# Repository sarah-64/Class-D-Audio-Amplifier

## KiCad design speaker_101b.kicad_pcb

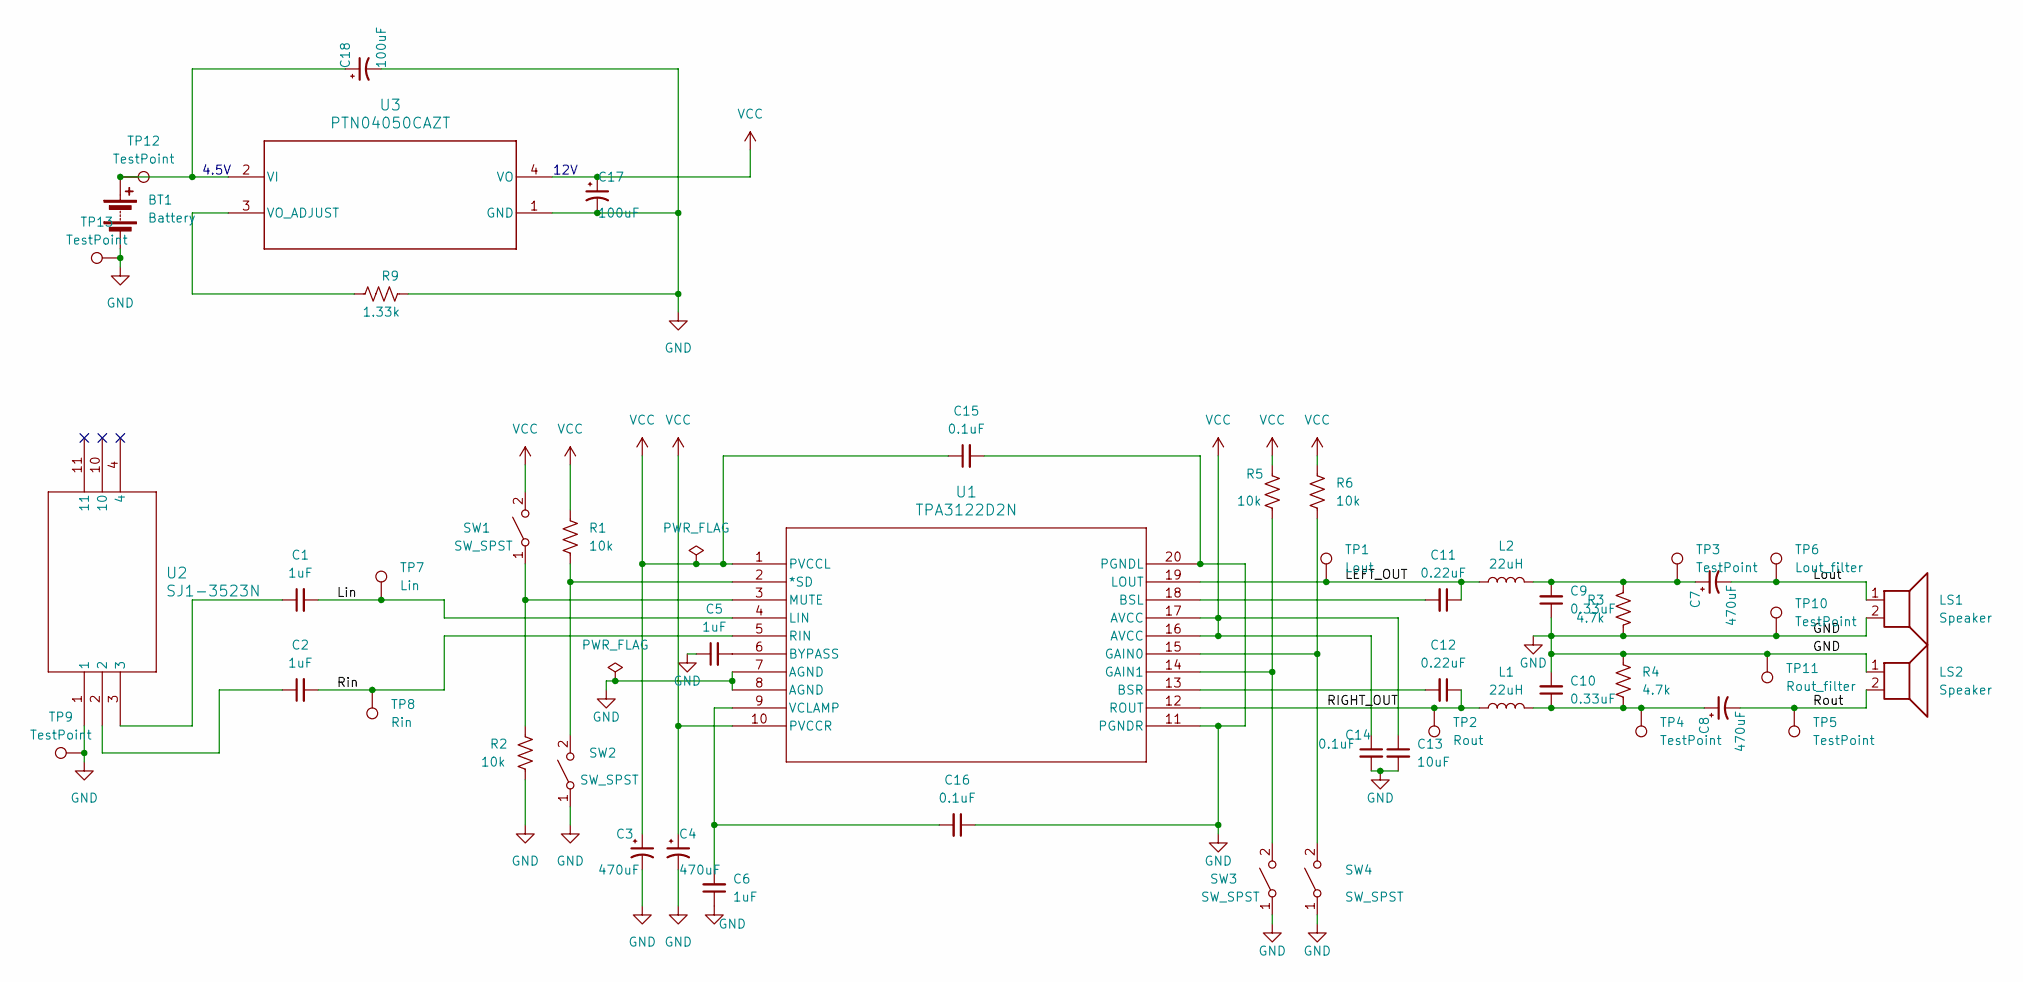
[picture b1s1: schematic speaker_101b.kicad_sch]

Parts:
BT1: Battery; R_1206_3216Metric_Pad1.30x1.75mm_HandSolder
C1, C2, C5, C6: 1uF; CAP_CL10_SAM
C3, C4, C7, C8: 470uF; CAP_EEE_J16_PAN
C9, C10: 0.33uF; CAP_CL10_SAM
C11, C12: 0.22uF; CAP_GCM155_MUR
C13: 10uF; CAP_CL10_SAM
C14: 0.1uF; CAP_CL10_SAM
C15, C16: 0.1uF; CC0805N_YAG
C17, C18: 100uF; CAP_CL10_SAM
L1, L2: 22uH; L_1206_3216Metric
LS1, LS2: Speaker; R_1206_3216Metric
R1, R2, R5, R6: 10k; R_1206_3216Metric
R3, R4: 4.7k; R_1206_3216Metric
R9: 1.33k; R_1206_3216Metric
SW1, SW2, SW3, SW4: SW_SPST; R_1206_3216Metric
TP1: Lout; TestPoint_Pad_3.0x3.0mm
TP2: Rout; TestPoint_Pad_3.0x3.0mm
TP3, TP4, TP5, TP9, TP10, TP12, TP13: TestPoint; TestPoint_Pad_3.0x3.0mm
TP6: Lout_filter; TestPoint_Pad_3.0x3.0mm
TP7: Lin; TestPoint_Pad_3.0x3.0mm
TP8: Rin; TestPoint_Pad_3.0x3.0mm
TP11: Rout_filter; TestPoint_Pad_3.0x3.0mm
U1: TPA3122D2N; N20
U2: SJ1-3523N; SJ1-3523N_CUD
U3: PTN04050CAZT; EUV0004A

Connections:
/LEFT_OUT: C11.1, L2.1, TP1.1, U1.19 (LOUT)
/Lin: C1.2, TP7.1, U1.4 (LIN)
/Lout: C7.2, LS1.1, TP6.1
/RIGHT_OUT: C12.1, L1.1, TP2.1, U1.12 (ROUT)
/Rin: C2.2, TP8.1, U1.5 (RIN)
/Rout: C8.2, LS2.2, TP5.1
GND: BT1.2 (-), C3.2, C4.2, C5.1, C6.1, C9.1, C10.2, C13.2, C14.2, C15.2, C16.1, C17.2, C18.2, LS1.2, LS2.1, R2.2, R3.2, R4.1, R9.2, SW2.1 (A), SW3.1 (A), SW4.1 (A), TP9.1, TP10.1, TP11.1, TP13.1, U1.7 (AGND), U1.8 (AGND), U1.11 (PGNDR), U1.20 (PGNDL), U2.1, U3.1 (GND)
unnamed: BT1.1 (+), C18.1, TP12.1, U3.2 (VI)
unnamed: C1.1, U2.3
unnamed: C2.1, U2.2
unnamed: C7.1, C9.2, L2.2, R3.1, TP3.1
unnamed: C8.1, C10.1, L1.2, R4.2, TP4.1
unnamed: R2.1, SW1.1 (A), U1.3 (MUTE)
unnamed: R1.2, SW2.2 (B), U1.2 (*SD)
unnamed: R5.2, SW3.2 (B), U1.14 (GAIN1)
unnamed: R6.2, SW4.2 (B), U1.15 (GAIN0)
unnamed: C11.2, U1.18 (BSL)
unnamed: C12.2, U1.13 (BSR)
unnamed: C5.2, U1.6 (BYPASS)
unnamed: C6.2, C16.2, U1.9 (VCLAMP)
unnamed: R9.1, U3.3 (VO_ADJUST)
VCC: C3.1, C4.1, C13.1, C14.1, C15.1, C17.1, R1.1, R5.1, R6.1, SW1.2 (B), U1.1 (PVCCL), U1.10 (PVCCR), U1.16 (AVCC), U1.17 (AVCC), U3.4 (VO)

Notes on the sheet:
4.5V
12V

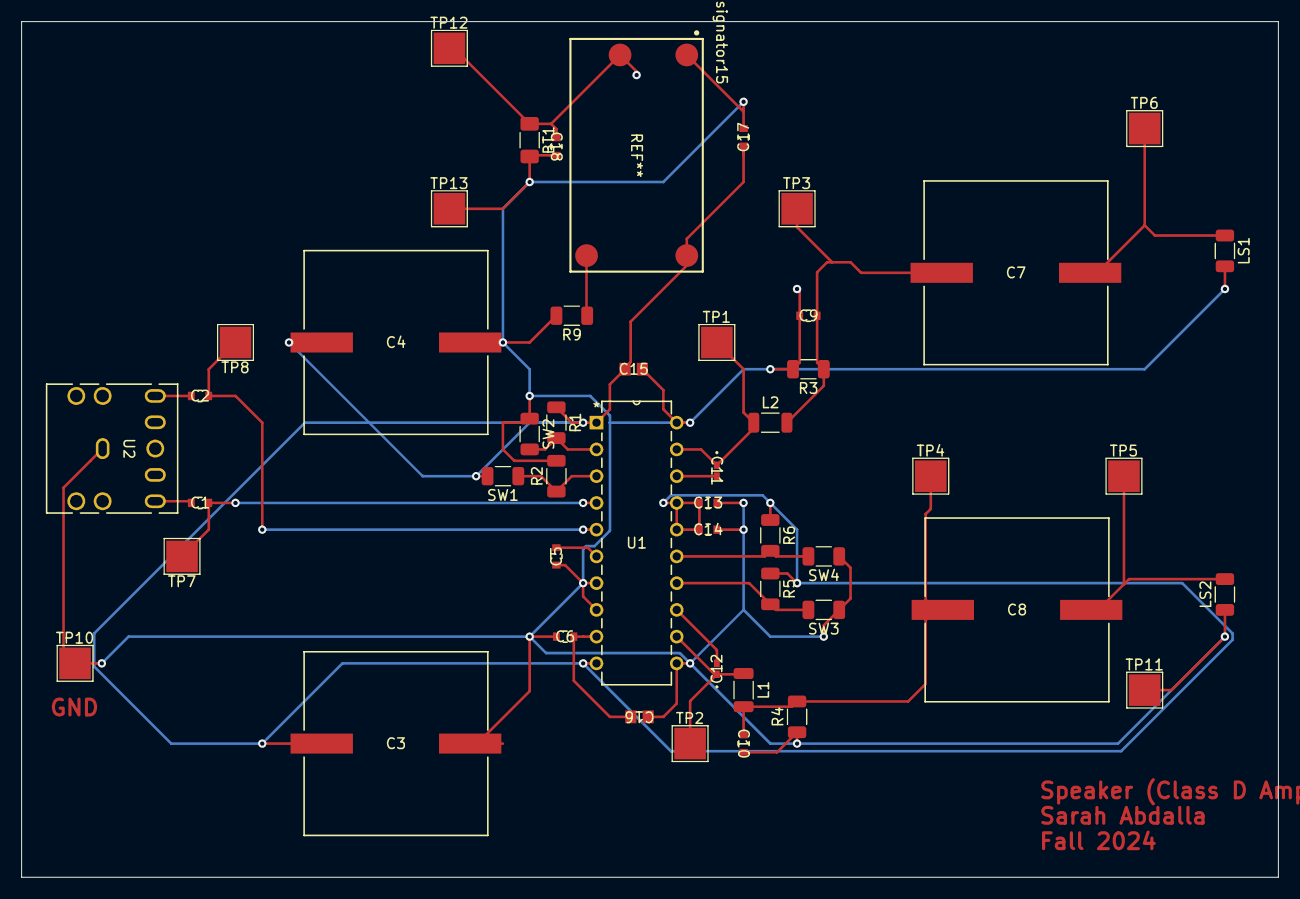
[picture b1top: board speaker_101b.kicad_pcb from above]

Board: 2 copper layers, 119.4 x 81.3 mm, 48 parts (0 on the bottom side), 21 nets.
